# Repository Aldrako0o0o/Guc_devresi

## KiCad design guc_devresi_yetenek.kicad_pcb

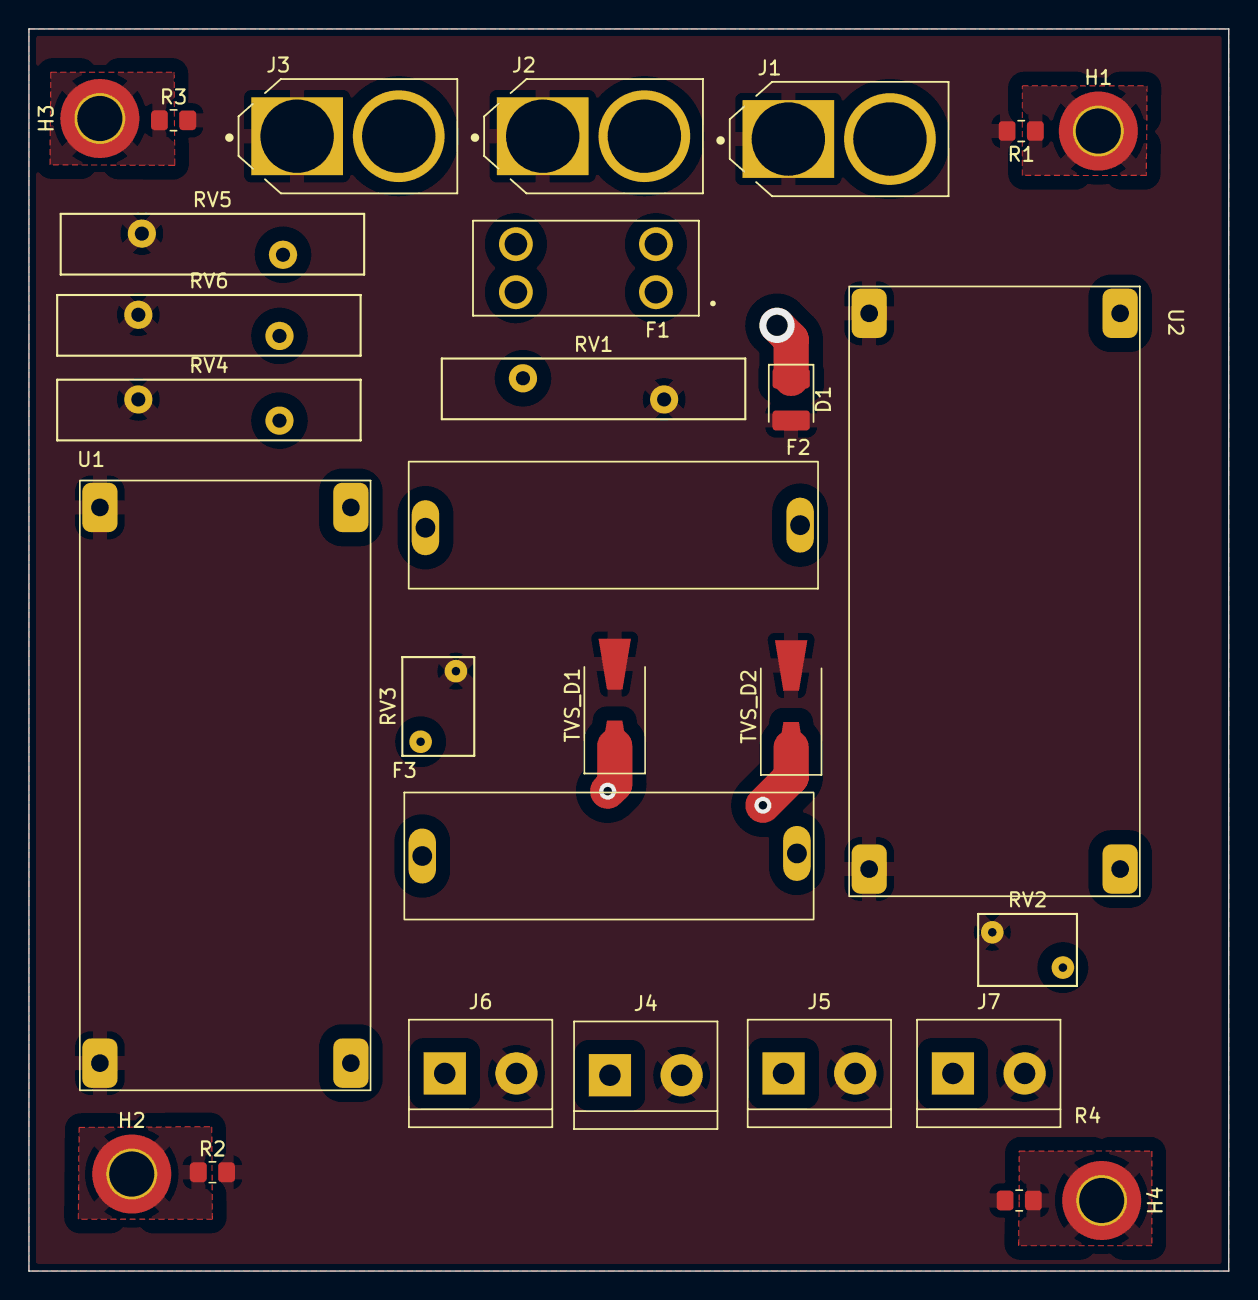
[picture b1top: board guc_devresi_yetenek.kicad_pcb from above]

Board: 2 copper layers, 85.0 x 88.0 mm, 29 parts (0 on the bottom side), 11 nets.

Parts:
D1: D; D_1210_3225Metric_Pad1.42x2.65mm_HandSolder
F1: Fuse_Small; FUSE_3568
F2, F3: Fuse; Fuse_holder
H1, H2, H3, H4: MountingHole_Pad; MountingHole_3.2mm_M3_DIN965_Pad_TopBottom
J1, J2, J3: XT60-M; AMASS_XT60-M
J4, J5, J6, J7: Terminal; TerminalBlock_bornier-2_P5.08mm
R1, R2, R3, R4: R_Small; R_0805_2012Metric_Pad1.20x1.40mm_HandSolder
RV1, RV4, RV5, RV6: Varistor; RV_Disc_D21.5mm_W4.3mm_P10mm
RV2, RV3: Varistor; RV_Disc_D7mm_W5.1mm_P5mm
TVS_D1, TVS_D2: D; D_SMA-SMB_Universal_Handsoldering
U1, U2: LM2596

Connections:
A: D1.1 (K), F1.1, J1.2 (+), J2.2 (+), RV1.2, U1.1 (IN+), U2.1 (IN+)
GND: D1.2 (A), J1.1 (-), J2.1 (-), J3.1 (-), J4.2, J5.2, J6.2, J7.2, R1.2, R2.2, R3.2, R4.2, RV1.1, RV2.2, RV3.1, RV4.2, RV5.2, RV6.2, TVS_D1.2 (A), TVS_D2.2 (A), U1.2 (IN-), U1.4 (OUT-), U2.2 (IN-), U2.4 (OUT-)
unnamed: F1.2, J3.2 (+), RV4.1, RV5.1, RV6.1
unnamed: F2.1, RV2.1, U2.3 (OUT+)
unnamed: F2.2, J4.1, J6.1, TVS_D1.1 (K)
unnamed: F3.1, RV3.2, U1.3 (OUT+)
unnamed: F3.2, J5.1, J7.1, TVS_D2.1 (K)
unnamed: H1.1, R1.1
unnamed: H2.1, R2.1
unnamed: H3.1, R3.1
unnamed: H4.1, R4.1
